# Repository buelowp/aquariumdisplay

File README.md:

# Using AndroidThings as a touchable Aquarium frontend

This is an attempt to connect to some micros I use to monitor my aquarium. It currently just provides a temperature and water level indication, but may include more sensors and details going forward.

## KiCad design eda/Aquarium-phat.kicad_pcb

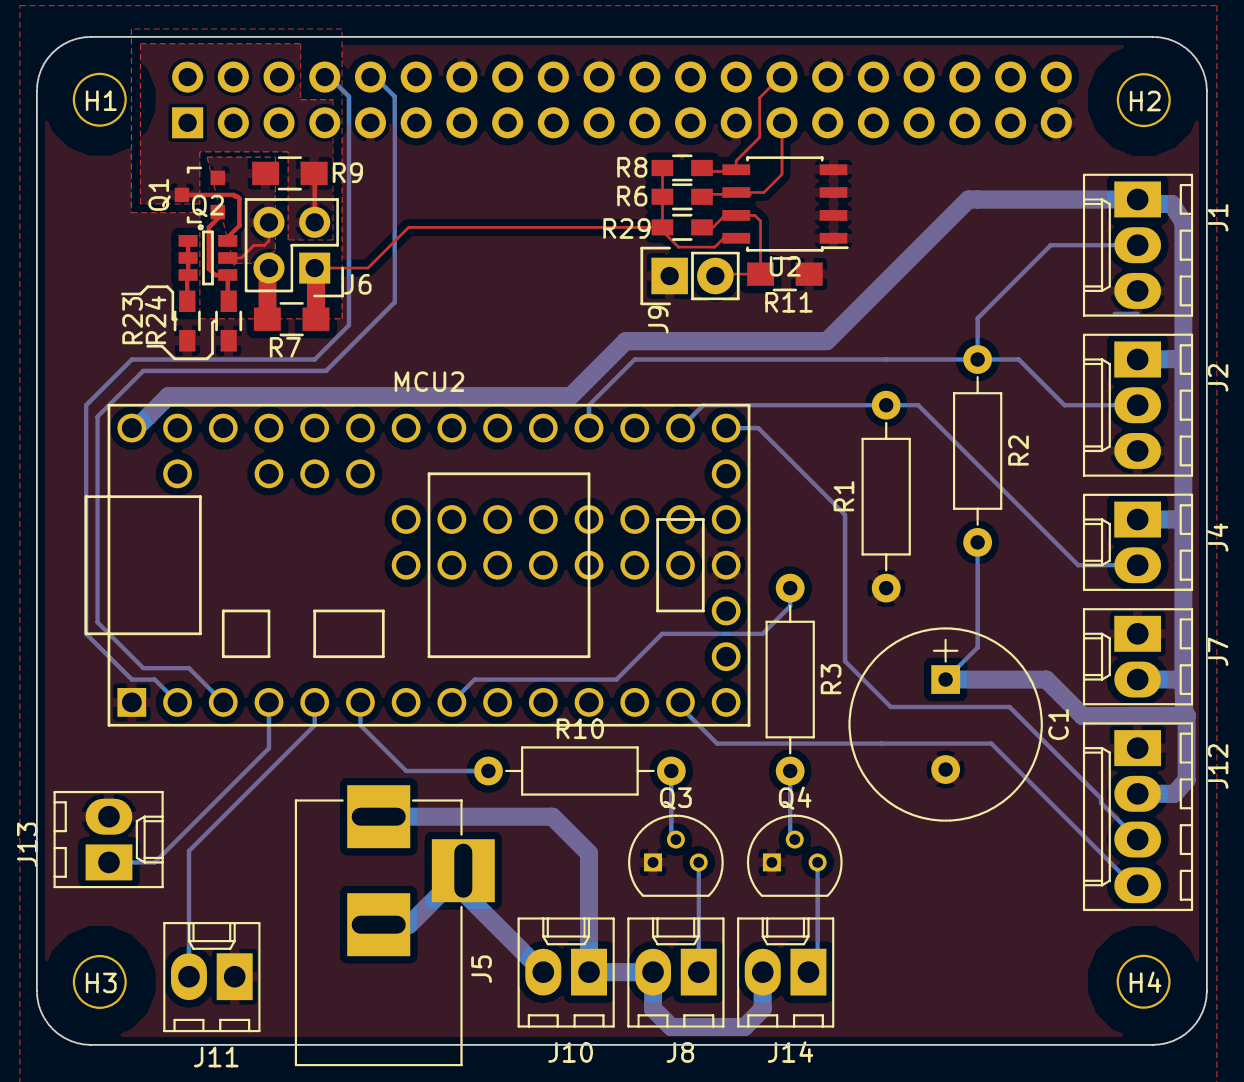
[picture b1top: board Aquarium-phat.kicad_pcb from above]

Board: 2 copper layers, 65.0 x 56.0 mm, 37 parts (1 on the bottom side), 27 nets.

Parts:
C1: 1000ohm; CP_Radial_Tantal_D10.5mm_P5.00mm
H1, H2, H3, H4: 3mm_Mounting_Hole; NPTH_3mm_ID
J1, J2: DS18B20; Molex_KK-6410-03_03x2.54mm_Straight
J3: 40HAT; Socket_Strip_Straight_2x20
J4: WTRLVL; Molex_KK-6410-02_02x2.54mm_Straight
J5: 12V; BARREL_JACK
J6: CONN_02X02; Pin_Header_Straight_2x02
J7: 5V_IN; Molex_KK-6410-02_02x2.54mm_Straight
J8, J14: UV_LED_STRIP; Molex_KK-6410-02_02x2.54mm_Straight
J9: CONN_01X02; Pin_Header_Straight_1x02
J10: 12V_OUT; Molex_KK-6410-02_02x2.54mm_Straight
J11: PUMP; Molex_KK-6410-02_02x2.54mm_Straight
J12: APA102; Molex_KK-6410-04_04x2.54mm_Straight
J13: HEATER; Molex_KK-6410-02_02x2.54mm_Straight
MCU2: Teensy3.1; Teensy30_31_32_LC
Q1: DMG2305UX; SOT-23
Q2: DMMT5401; SOT-23-6
Q3, Q4: 2N3904; TO-92_Molded_Narrow
R1: 750; R_Axial_DIN0207_L6.3mm_D2.5mm_P10.16mm_Horizontal
R2: 10k; R_Axial_DIN0207_L6.3mm_D2.5mm_P10.16mm_Horizontal
R3, R10: 1k; R_Axial_DIN0207_L6.3mm_D2.5mm_P10.16mm_Horizontal
R6, R8: 3.9K; R_0603_HandSoldering
R7, R9, R11: DNP; R_0805_HandSoldering
R23, R24: 22; R_0603_HandSoldering
R29: 10K; R_0603_HandSoldering
U2: CAT24C32; SOIC-8_3.9x4.9mm_Pitch1.27mm

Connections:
/ID_SC_EEPROM: J3.28, R8.2, U2.5
/ID_SD_EEPROM: J3.27, R6.2, U2.6
/P3V3: J6.1, R6.1, R7.2, R8.1, R29.1, U2.8
/P3V3_HAT: J3.1, J6.2, R7.1
/P5V: J6.3, Q1.3, Q2.6, R9.2
/P5V_HAT: J3.2, J3.4, J6.4, Q1.2, Q2.5, R9.1
/Teensy/1WIRE: J1.2, J2.2, MCU2.23, R2.1
/Teensy/HTR_EN: J13.1, MCU2.4
/Teensy/PUMP_EN: J11.2, MCU2.5
GND: C1.2, J1.3, J2.3, J3.6, J3.9, J3.14, J3.20, J3.25, J3.30, J3.34, J3.39, J7.1, J9.1, J11.1, J12.1, J13.2, MCU2.1, MCU2.17, Q3.1, Q4.1, R1.1, R11.2, R23.2, R24.2, U2.1, U2.2, U2.3, U2.4
unnamed: J4.2, MCU2.21, R1.2
unnamed: J8.1, Q3.3
unnamed: J9.2, R11.1, R29.2, U2.7
unnamed: J5.1, J8.2, J10.1, J14.2
unnamed: J5.2, J5.3, J10.2
unnamed: J12.3, MCU2.20
unnamed: J12.4, MCU2.13
unnamed: J14.1, Q4.3
unnamed: Q1.1, Q2.4, R24.1
unnamed: Q2.1, Q2.2, Q2.3, R23.1
unnamed: Q3.2, R10.2
unnamed: Q4.2, R3.2
P5V_HAT: C1.1, J1.1, J2.1, J4.1, J7.2, J12.2, MCU2.33, R2.2
RX: J3.10, MCU2.3
TX: J3.8, MCU2.2
UV_EN1: MCU2.6, R10.1
UV_EN2: MCU2.8, R3.1

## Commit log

2017-05-03 Initial commit of code
2017-05-03 First real pass at the app outline
2017-05-03 Getting things moving
2017-05-03 More work to displaying fish information
2017-05-03 Got the webview mostly working now. Adding DataView stuff
2017-05-03 Beginnings of a data view for aquarium data
2017-05-04 More usability fixes
    Added the pump state to the data view
    Added swipe to exit the data view
2017-05-05 More useability changes
    Integrated the Neopixel BB library
    Integrated my sunset calculator
    Addition of the Lights class to handle the lights
2017-05-17 Added FastLED SPI support Updated a bit
2017-05-18 Fixing bug with opening .html files
2017-05-19 Fixes and whatnot
2017-05-23 Debug updates and bug fixes
    Switch to embedded qt5.8
    Got fonts working
    Got swipe with 3 fingers working
2017-05-23 Cleanup and get swipe and tap workingwq
2017-07-11 Cleaning up prior to making this a different project
2017-07-11 Initial population
    Contains the Arduino project for the Teensy controller
    Contains the KiCad project files for the pi-hat
    Contains the Android Things project files
2017-07-13 Fixing some names for Android Studio use
2017-07-13 Simple Updates. Checking to see how this worked
2017-07-13 One more change with a fixed git path
2017-07-15 Working on messaging format a bit. Added a per message size to allow for more realistic parsing.
2017-07-16 Lots of fixes
    Fixed time handling in Settings
    Fixed how we move messages around a bit more
    Added GUI fields into settings view
2017-07-16 More fixes
    Getting serial comm to work mostly.
    Added new Teensy class to manage constructing a message
    Fixed up parsing messages a bit, more to come
2017-07-17 More stuff works
    Temp and button state now get to settings
    Fixed lots of bugs related to messages and sending
    Need to go back to find a way to combine messages and remove flush()
2017-07-17 Adding in a first pass at timing out the activity with no activity
2017-07-18 Updating the README.md, and adding a little bit of code
    Fixed the moonphase calculator. Much closer to accurate, but not done
    Added the UI timeout to LightsActivity
2017-07-19 Fixed a bug
    Seems calling finish on the Activity view does not work if you set the
    view window earlier. Removed those, and updated the flick to do the
    right thing.
2017-07-21 Functional improvements
    Can now toggle the UV lights when connected
    State of lights and LED brightness now go back and forth
    Lights_Activity has correct timeouts and button timeout resets
2017-07-21 Functional improvements
    Brightness slider now works.
2017-07-21 Updated the README
2017-07-21 Bug fixes
    Code cleanup
    Bug fixes
    a bit of refactoring
2017-07-21 Improving useability
    Added the ability to toggle all the lights using the specified buttons
2017-07-23 Beginning to program the LEDs for light activity
2017-07-27 Lots of changes
    Adding and updating features, like RGB display
    Updated and fixed messaging with the Teensy
    Added an RGB getter to Teensy, and updated how I turn on/off lights
    Bugfixes
    Probably other things I am forgetting about
2017-07-29 New work towards making the LEDs work, and bugfixes
2017-07-31 Lots of stuff done here
    Fixed a bug setting the brightness
    Fixed a bug which caused the UV lights to be backwards
    Added a bunch of new messaging to be more explicity
    Other stuff I've already forgotten about
2017-12-11 Getting back up to speed
    Updated to more recent Things API version
    Added LED control for APA102 strings
    Added ADC via SPI chip MCP3008 support
    Added some contrib drivers to the system
2017-12-12 Continuing the effort.
    Working on getting WebView to work, it's partial
    Did some work to add APA stuff
    Updated to the latest
2017-12-20 Adding the MyWebView class
2019-05-03 Getting closer
    * Now I can get MQTT messages, but it's still not working right
    * TextView objects never update
2019-05-04 Migrating to a new design for my MQTT implementation.
    * Got this from someone who knows how to do it better than me, hope it works
2019-05-04 Cleaning up the class a bit to match my code style
2019-05-04 More cleanups and added subscription strings
2019-05-07 Fixups
    * Added working MQTT service
    * Connected MQTT service to activities
    * Added androidx capability
    * Cleaned up some naming
2019-05-07 Updating readme
2019-05-07 Adding view timeouts
2019-05-07 Beginning work on WebView for displaying details about the current fish
2019-05-11 Got the webivew doing what I wanted
    * Swiping works now
    * Still needs a timeout
2019-05-12 Fixed some timeout issues on views
    * Make MainView correctly turn off when another view exits
2019-06-22 Adding some new data members
2019-06-22 Changes I can't identify
2019-06-27 Merge branch 'master' of https://github.com/buelowp/aquarium
    * Added a new controls view
    * Able to publish messages from Activities now
    * Cleanup usage of constants
    * Should be able to turn the pump on and off now
    # Conflicts:
    # app/src/main/java/com/home/pete/aquarium/AquariumReceiverService.java
2019-08-18 Issue #1: Adding new tracking capabilities
